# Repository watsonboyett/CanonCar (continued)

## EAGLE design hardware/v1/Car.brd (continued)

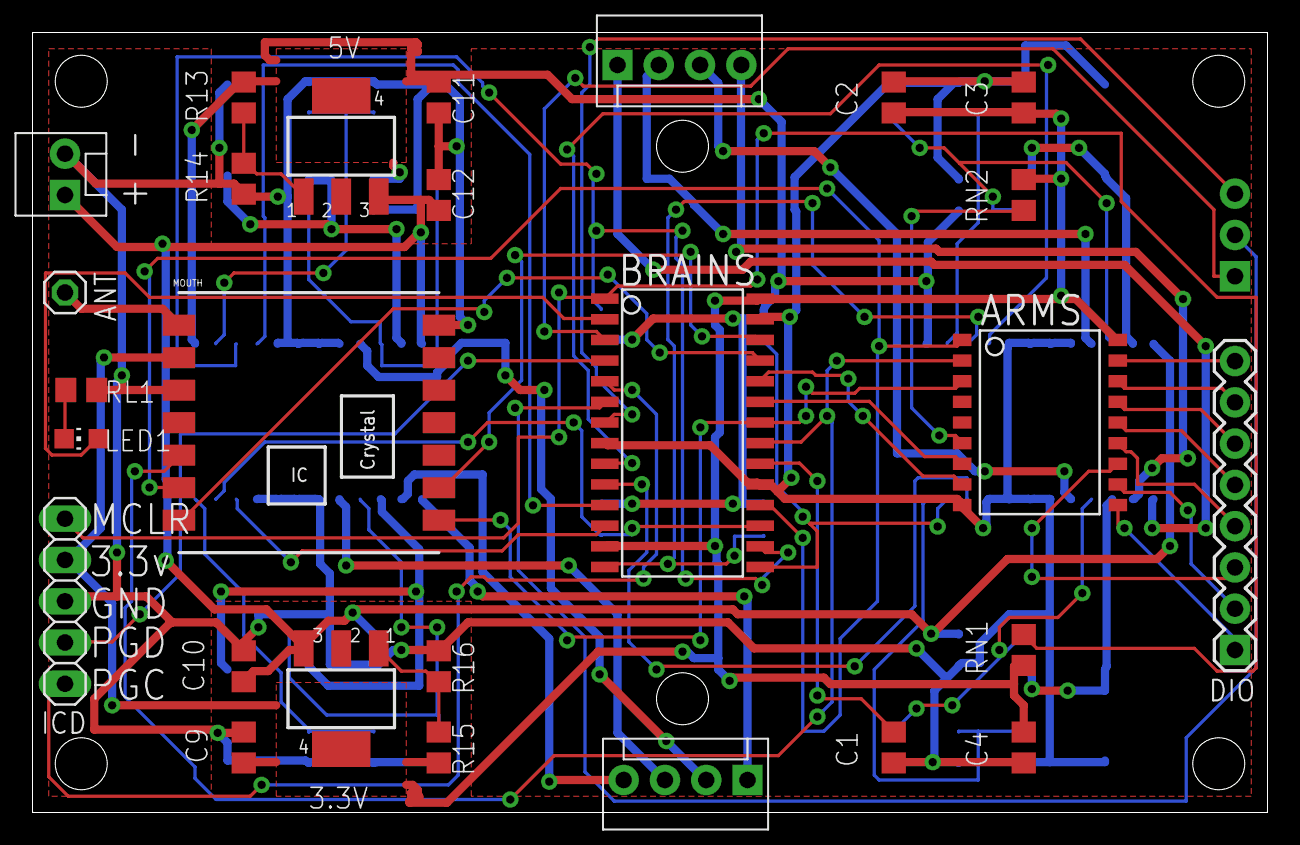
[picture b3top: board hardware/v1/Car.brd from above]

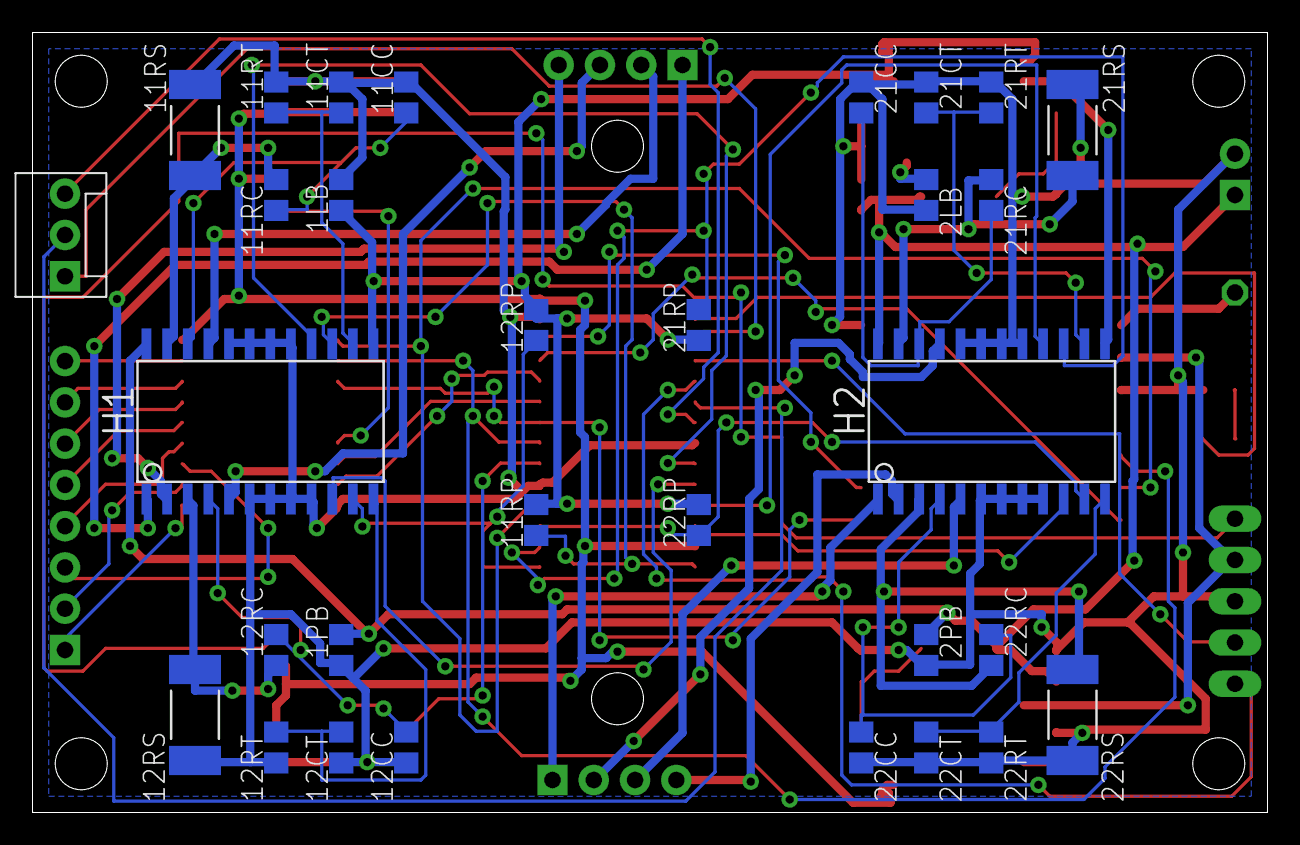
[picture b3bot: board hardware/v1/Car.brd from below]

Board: 2 copper layers, 76.0 x 48.0 mm, 58 parts (31 on the bottom side), 60 nets.

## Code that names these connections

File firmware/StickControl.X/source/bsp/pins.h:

#ifndef PINS_H
#define	PINS_H

#include <stdint.h>
#include <stdbool.h>


#define A0      (&Pin_RA0)
#define A1      (&Pin_RA1)
#define A2      (&Pin_RA2)
#define A3      (&Pin_RA3)
#define A4      (&Pin_RA4)
#define A5      (&Pin_RB2)
#define A6      (&Pin_RB3)
#define A7      (&Pin_RB4)


#define SCLK    (&Pin_RB9)
#define MOSI    (&Pin_RB10)
#define MISO    (&Pin_RB11)
#define DIO_CS  (&Pin_RB12)
#define DIO_IRQ (&Pin_RB13)
#define RFM_CS  (&Pin_RB14)
#define RFM_IRQ (&Pin_RB15)


#define D0      (&Pin_D0)
#define D1      (&Pin_D1)
#define D2      (&Pin_D2)
#define D3      (&Pin_D3)
#define D4      (&Pin_D4)
#define D5      (&Pin_D5)
#define D6      (&Pin_D6)
#define D7      (&Pin_D7)

#define M1_PHASE1   (&Pin_M0)
#define M1_PHASE2   (&Pin_M1)
#define M1_I0X      (&Pin_M2)
#define M1_I1X      (&Pin_M3)
#define M2_PHASE1   (&Pin_M4)
#define M2_PHASE2   (&Pin_M5)
#define M2_I0X      (&Pin_M6)
#define M2_I1X      (&Pin_M7)

#define M1_VREF1    (&Pin_RB5)
#define M1_VREF2    (&Pin_RB6)
#define M2_VREF1    (&Pin_RB7)
#define M2_VREF2    (&Pin_RB8)


typedef volatile uint16_t * const RegAddr_t;

typedef enum {
    Internal,
    SPI_DIO
} PortLoc_e;

typedef enum {
    Digital,
    Analog
} PinMode_e;

typedef enum {
    Output = 0,
    Input = 1,
    Input_Pullup = 2,
    Output_OpenCollector = 3
} PinDir_e;

typedef struct {
    const PortLoc_e location; // pin's location (internal/spi)
    const uint8_t addr; // pin's base/device address
    RegAddr_t tris; // pin's port direction register address
    RegAddr_t port; // pin's port read register address
    RegAddr_t latch; // pin's port write register address
    const uint8_t bit_pos; // pin's bit position within port
    const uint8_t analog_chan; // pin's analog channel (if present)
} PinInfo_s;

typedef struct {
    PinInfo_s * const info;
    PinMode_e mode;
    PinDir_e dir;
} PinConfig_s;


PinInfo_s * get_pin_info(PinConfig_s * pin);
PinMode_e get_pin_mode(PinConfig_s * pin);
PinDir_e get_pin_dir(PinConfig_s * pin);



// NOTE: must define pins (declared in C source file)
// TODO: is there a better way of managing the pins than this?
extern PinConfig_s Pin_RA0;
extern PinConfig_s Pin_RA1;
extern PinConfig_s Pin_RA2;
extern PinConfig_s Pin_RA3;
extern PinConfig_s Pin_RA4;
extern PinConfig_s Pin_RB0;
extern PinConfig_s Pin_RB1;
extern PinConfig_s Pin_RB2;
extern PinConfig_s Pin_RB3;
extern PinConfig_s Pin_RB4;
extern PinConfig_s Pin_RB5;
extern PinConfig_s Pin_RB6;
extern PinConfig_s Pin_RB7;
extern PinConfig_s Pin_RB8;
extern PinConfig_s Pin_RB9;
extern PinConfig_s Pin_RB10;
extern PinConfig_s Pin_RB11;
extern PinConfig_s Pin_RB12;
extern PinConfig_s Pin_RB13;
extern PinConfig_s Pin_RB14;
extern PinConfig_s Pin_RB15;


extern PinConfig_s Pin_D0;
extern PinConfig_s Pin_D1;
extern PinConfig_s Pin_D2;
extern PinConfig_s Pin_D3;
extern PinConfig_s Pin_D4;
extern PinConfig_s Pin_D5;
extern PinConfig_s Pin_D6;
extern PinConfig_s Pin_D7;

extern PinConfig_s Pin_M0;
extern PinConfig_s Pin_M1;
extern PinConfig_s Pin_M2;
extern PinConfig_s Pin_M3;
extern PinConfig_s Pin_M4;
extern PinConfig_s Pin_M5;
extern PinConfig_s Pin_M6;
extern PinConfig_s Pin_M7;




#endif

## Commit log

2013-07-01 initial commit of exiting project
2014-11-26 Uhh... Not really sure what's changed...
2014-12-01 Completed Rev.A of v2 hardware.
2014-12-14 Checkpointing. (about to make so potentially dangerous changes.)
2014-12-14 Fixed a number of issues discovered from Rev. A boards.
2014-12-15 Minor cleanup.
2014-12-21 Updating for new V2 hardware (not working yet).
2014-12-21 redecorating the folder structures.
2015-04-24 Fixed motor control functions. Cleaned up formatting and type declarations.
2015-04-24 Removed dependence on types.h file, now using stdint.h
2015-04-24 More code cleanup.
2015-04-24 Attempting to improve IO capabilities (by making them more API-like).
2015-04-24 checkpointing
2015-04-25 Fixed PGD/PGC error (swapped) in schematic.
2015-04-28 Fixed external (spi) digital io functions.
2015-04-28 Refactored digitalio a bit.
2015-04-28 More refactoring.
2015-04-28 Even more refactoring.
2015-04-29 Fixed analog io functions.
2015-04-29 Swapped non-analog input pins for ones that do support analog input. Significantly cleaned up schematic.
2015-04-30 Added more pin definitions.
2015-04-30 Added image of v2rB schematic for reference.
2015-05-01 Fixed spurrious spi write issue. Started working on motor library.
2015-05-06 Added eagle library containing various microchip parts.
2015-05-07 More schematic and layout cleanup.
2015-05-08 Adding low pass filters to PWM outputs (for motor VREF).
2015-05-09 More updates to schematic and layout. Checkpointing.
2015-05-22 Fixed motor current level enums. Delay functions still broken (maybe more broken now).
2015-05-22 Checkpointing.
2015-05-30 Started routing pcb for reals.
2015-06-08 Routed power traces.
2015-06-09 Finished routing power signals.
2015-06-09 Added design rule file and hardware notes.
2015-06-11 Fixed bug where SPI IO chips were ignoring their HW addresses.
2015-06-12 'Fixed' delay functions. They now provide the correct delay intervals, but are very hardware specific.
2015-08-31 Finalized(-ish) routing for V2
2015-11-19 Added v3 files. Still WIP.
2015-11-19 Updates to v2? I don't really know. It's ben a while...
2015-11-20 Started layout for v3.
2015-11-21 Continued working layout. Added USB components. Remapped some pins.
2015-11-21 More routing (~50% complete). Normalized/placed texts.
2015-12-06 Minor board tweaks.
2015-12-06 Reorganized firmware file structure. Fixed SPI read/write methods.
2015-12-07 Fixed some quirks with analog read functions. Added test app for wired remote control of car.
2015-12-07 Re-added project config files (they became ignored after the re-org).
2015-12-07 Minor tweaks to layout/DRU. Changed via stop mask values.
2015-12-22 Finished routing power for motor driver 1.
2016-01-06 Finished routing power lines and other significant signals.
2016-01-06 Fixed some part values. Cleaned up schematic and board names/values.
2018-09-07 Added revision history notes
